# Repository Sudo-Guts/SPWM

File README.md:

# SPWM — Inversor trifásico

Proyecto de control y etapa de potencia de un inversor trifásico con modulación sinusoidal por ancho de pulso (SPWM).

## Objetivo

Generar tres señales de control con desfases de 120 grados mediante un microcontrolador ATmega328P, para gobernar las tres ramas de un inversor trifásico mediante drivers de compuerta.

## Hardware actual

- Microcontrolador: ATmega328P.
- Cristal en el esquema: 16 MHz. Los fusibles y la frecuencia efectiva aún deben verificarse.
- Drivers: tres IR2109.
- Etapa de potencia: seis MOSFET. El esquema identifica IRF540N; el componente físico previsto es IRF640N. Es necesario comprobar compatibilidad de pinout, huella, manejo de compuerta y especificaciones antes de validar la placa.
- Alimentación de potencia prevista: 28 V, fuente externa limitada.

## Estructura

```text
SPWM/
├── .gitignore
├── README.md
├── C0DE/
│   ├── Makefile
│   ├── inc/
│   ├── src/
│   └── out/
├── DOC/
│   └── CheckList.txt
├── PCB/
│   ├── SPWM.kicad_pro
│   ├── SPWM.kicad_sch
│   ├── SPWM.kicad_pcb
│   └── fabrication/
└── SIM/
    ├── psim/
    └── spice/
        └── models/
```

- **C0DE/**: firmware y compilación con AVR-GCC y GNU Make.
- **DOC/**: seguimiento del proyecto mediante `CheckList.txt`, tareas por etapas y criterios de validación.
- **PCB/**: proyecto editable de KiCad; `fabrication/` contiene archivos de salida existentes, no aprobados todavía para fabricar.
- **SIM/psim/**: modelos y circuitos de simulación en PSIM.
- **SIM/spice/**: simulaciones eléctricas SPICE; `models/` guarda los modelos de componentes utilizados.

## Estado del borrador

El firmware incluido es solo un punto de partida que permanece sin PWM ni habilitación de los drivers. No representa la implementación SPWM final. Los archivos de KiCad se recuperaron del proyecto existente en Drive. Falta comprobar ERC/DRC, huellas, pads, asignación de pines, conexión de potencia y sincronización PWM antes de usar la placa o los Gerbers para fabricar.

## Compilación (cuando se disponga de Linux + avr-gcc)

```sh
cd C0DE
make
make size
make clean
```

El Makefile supone F_CPU = 16 MHz para la compilación; verificar primero la fuente de reloj real y los fusibles del ATmega328P.

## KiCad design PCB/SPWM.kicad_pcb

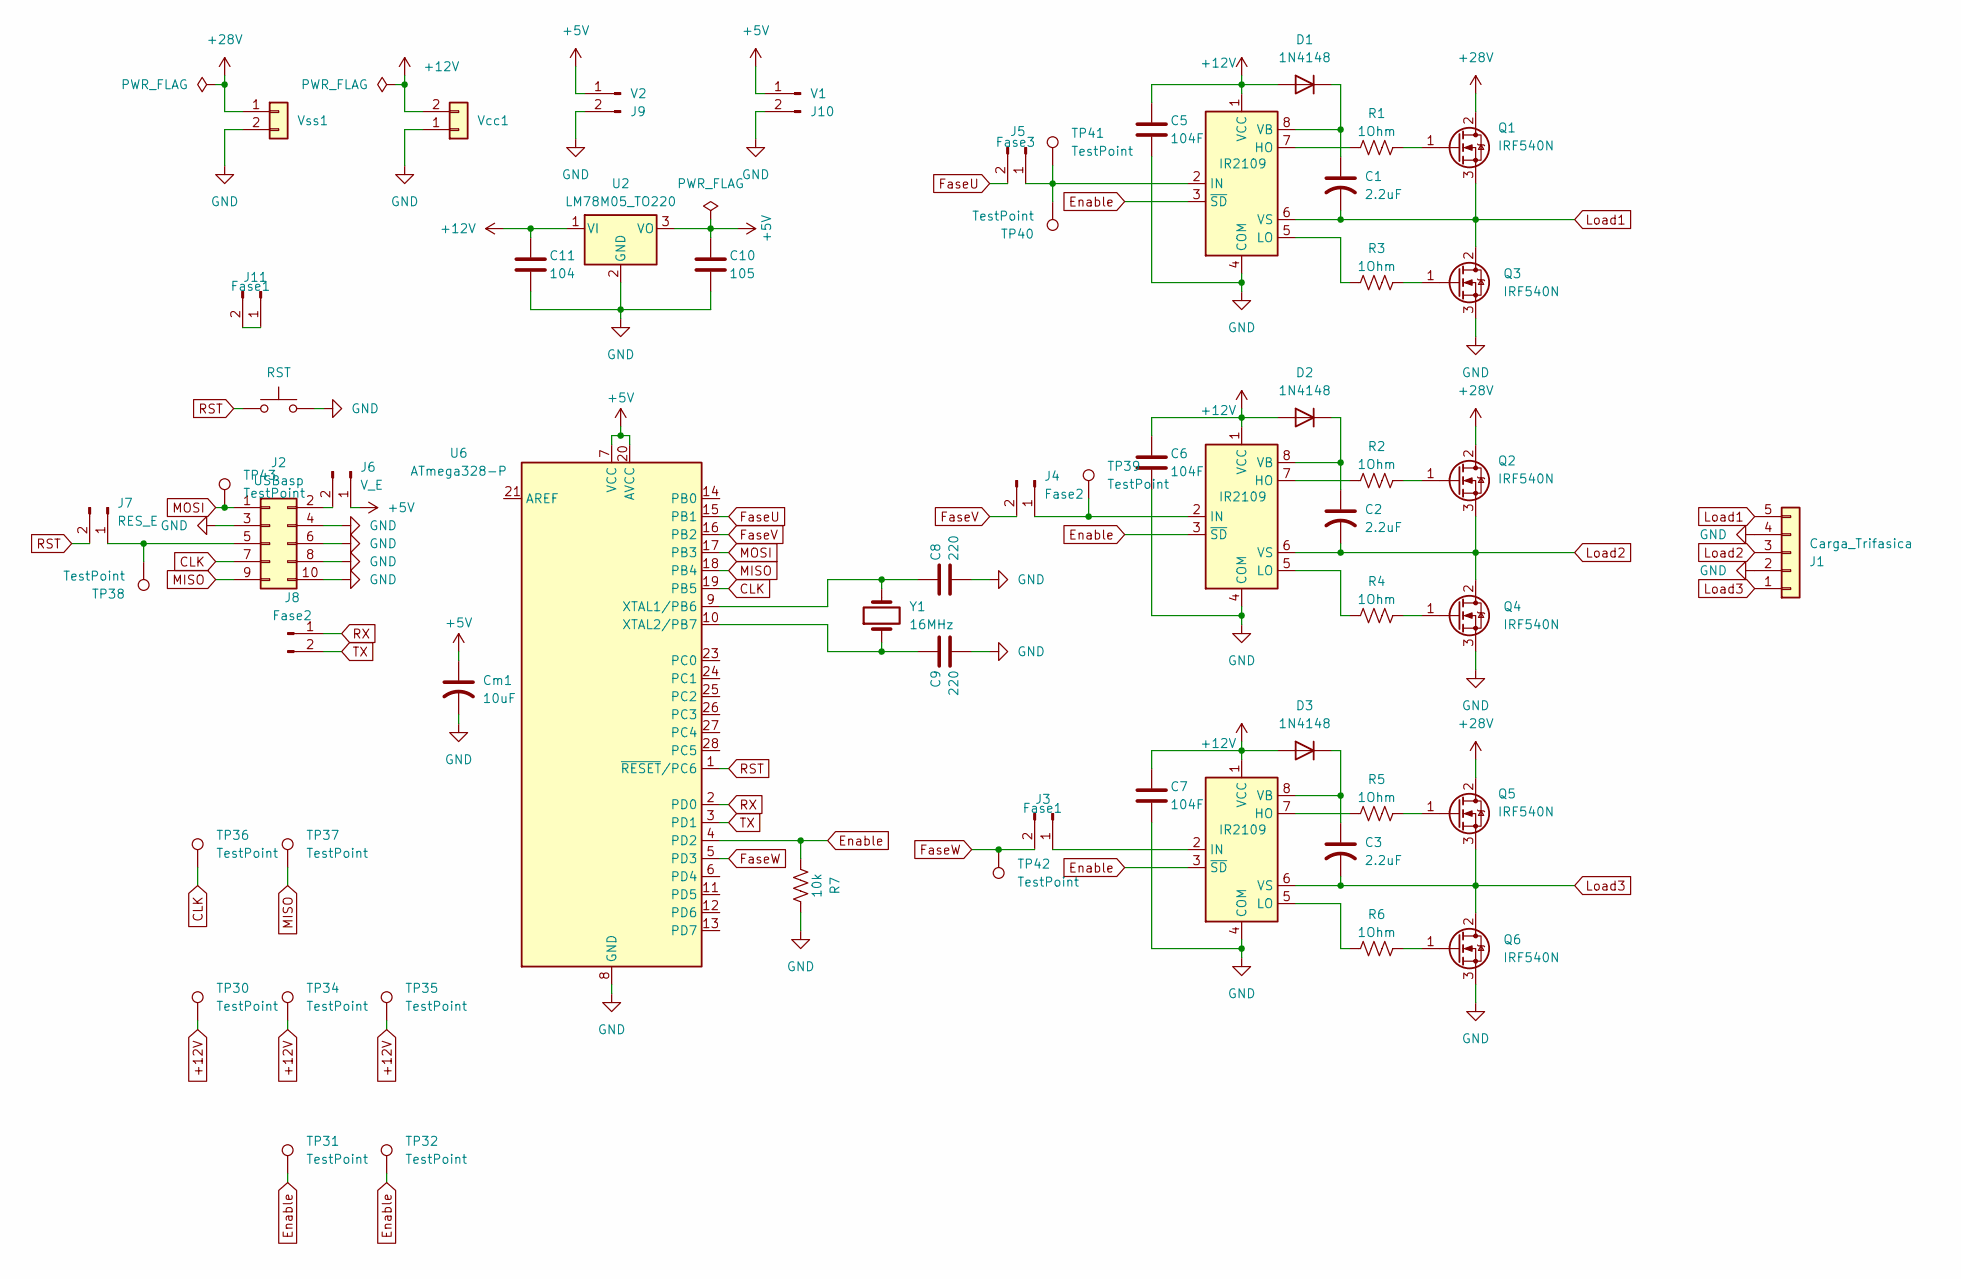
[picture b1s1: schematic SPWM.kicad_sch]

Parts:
C1, C2, C3: 2.2uF; CP_Radial_D4.0mm_P2.00mm
C5, C6, C7: 104F; CP_Radial_Tantal_D5.0mm_P5.00mm
C8, C9: 220; CP_Radial_Tantal_D5.0mm_P5.00mm
C10: 105; CP_Radial_Tantal_D5.0mm_P5.00mm
C11: 104; CP_Radial_Tantal_D5.0mm_P5.00mm
Cm1: 10uF; CP_Radial_D4.0mm_P2.00mm
D1, D2, D3: 1N4148; D_DO-35_SOD27_P7.62mm_Horizontal
J1: Carga_Trifasica; TerminalBlock_MaiXu_MX126-5.0-05P_1x05_P5.00mm
J2: USBasp; IDC-Header_2x05_P2.54mm_Vertical
J3, J11: Fase1; PinHeader_1x02_P2.54mm_Vertical
J4, J8: Fase2; PinHeader_1x02_P2.54mm_Vertical
J5: Fase3; PinHeader_1x02_P2.54mm_Vertical
J6: V_E; PinHeader_1x02_P2.54mm_Vertical
J7: RES_E; PinHeader_1x02_P2.54mm_Vertical
J9: V2; PinHeader_1x02_P2.54mm_Vertical
J10: V1; PinHeader_1x02_P2.54mm_Vertical
Q1, Q2, Q3, Q4, Q5, Q6: IRF540N; TO-220-3_Vertical
R1, R2, R3, R4, R5, R6: 1Ohm; R_Axial_DIN0309_L9.0mm_D3.2mm_P12.70mm_Horizontal
R7: 10k; R_Axial_DIN0309_L9.0mm_D3.2mm_P12.70mm_Horizontal
SW1: RST; SW_PUSH_6mm_H7.3mm
TP30, TP31, TP32, TP34, TP35, TP36, TP37, TP38, TP39, TP40, TP41, TP42, TP43: TestPoint; TestPoint_Bridge_Pitch7.62mm_Drill1.3mm
U1, U4, U5: IR2109; DIP-8_W7.62mm_Socket
U2: LM78M05_TO220; TO-220-3_Vertical
U6: ATmega328-P; DIP-28_W7.62mm
Vcc1: Conn_01x02; TerminalBlock_MaiXu_MX126-5.0-02P_1x02_P5.00mm
Vss1: Conn_01x02; TerminalBlock_MaiXu_MX126-5.0-02P_1x02_P5.00mm
Y1: 16MHz; Crystal_HC49-4H_Vertical

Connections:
+5V: C10.1, Cm1.1, J6.1, J9.1 (Pin_1_1), J10.1 (Pin_1_1), U2.3 (VO), U6.7 (VCC), U6.20 (AVCC)
+12V: C5.1, C6.1, C7.1, C11.1, D1.2 (A), D2.2 (A), D3.2 (A), TP30.1 (1_1), TP34.1 (1_1), TP35.1 (1_1), U1.1 (VCC), U2.1 (VI), U4.1 (VCC), U5.1 (VCC), Vcc1.2 (Pin_2_2)
+28V: Q1.2 (D), Q2.2 (D), Q5.2 (D), Vss1.1 (Pin_1_1)
CLK: J2.7, TP36.1 (1_1), U6.19 (PB5)
Enable: R7.1, TP31.1 (1_1), TP32.1 (1_1), U1.3 (~SD), U4.3 (~SD), U5.3 (~SD), U6.4 (PD2)
FaseU: J5.2, U6.15 (PB1)
FaseV: J4.2, U6.16 (PB2)
FaseW: J3.2, TP42.1 (1_1), U6.5 (PD3)
Load1: C1.2, J1.5, Q1.3 (S), Q3.2 (D), U1.6 (VS)
Load2: C2.2, J1.3, Q2.3 (S), Q4.2 (D), U4.6 (VS)
Load3: C3.2, J1.1, Q5.3 (S), Q6.2 (D), U5.6 (VS)
MISO: J2.9, TP37.1 (1_1), U6.18 (PB4)
MOSI: J2.1, TP43.1 (1_1), U6.17 (PB3)
unnamed: C1.1, D1.1 (K), U1.8 (VB)
unnamed: C2.1, D2.1 (K), U4.8 (VB)
unnamed: C3.1, D3.1 (K), U5.8 (VB)
unnamed: J2.2, J6.2
unnamed: J2.5, J7.1, TP38.1 (1_1)
unnamed: J3.1, U5.2 (IN)
unnamed: J4.1, TP39.1 (1_1), U4.2 (IN)
unnamed: J5.1, TP40.1 (1_1), TP41.1 (1_1), U1.2 (IN)
unnamed: J11.1, J11.2
unnamed: Q1.1 (G), R1.2
unnamed: Q2.1 (G), R2.2
unnamed: Q3.1 (G), R3.2
unnamed: Q4.1 (G), R4.2
unnamed: Q5.1 (G), R5.2
unnamed: Q6.1 (G), R6.2
unnamed: R1.1, U1.7 (HO)
unnamed: R3.1, U1.5 (LO)
unnamed: R2.1, U4.7 (HO)
unnamed: R4.1, U4.5 (LO)
unnamed: R5.1, U5.7 (HO)
unnamed: R6.1, U5.5 (LO)
unnamed: C8.1, U6.9 (XTAL1/PB6), Y1.2
unnamed: C9.1, U6.10 (XTAL2/PB7), Y1.1
RST: J7.2, SW1.1 (1_1), U6.1 (~RESET/PC6)
RX: J8.1, U6.2 (PD0)
TX: J8.2, U6.3 (PD1)

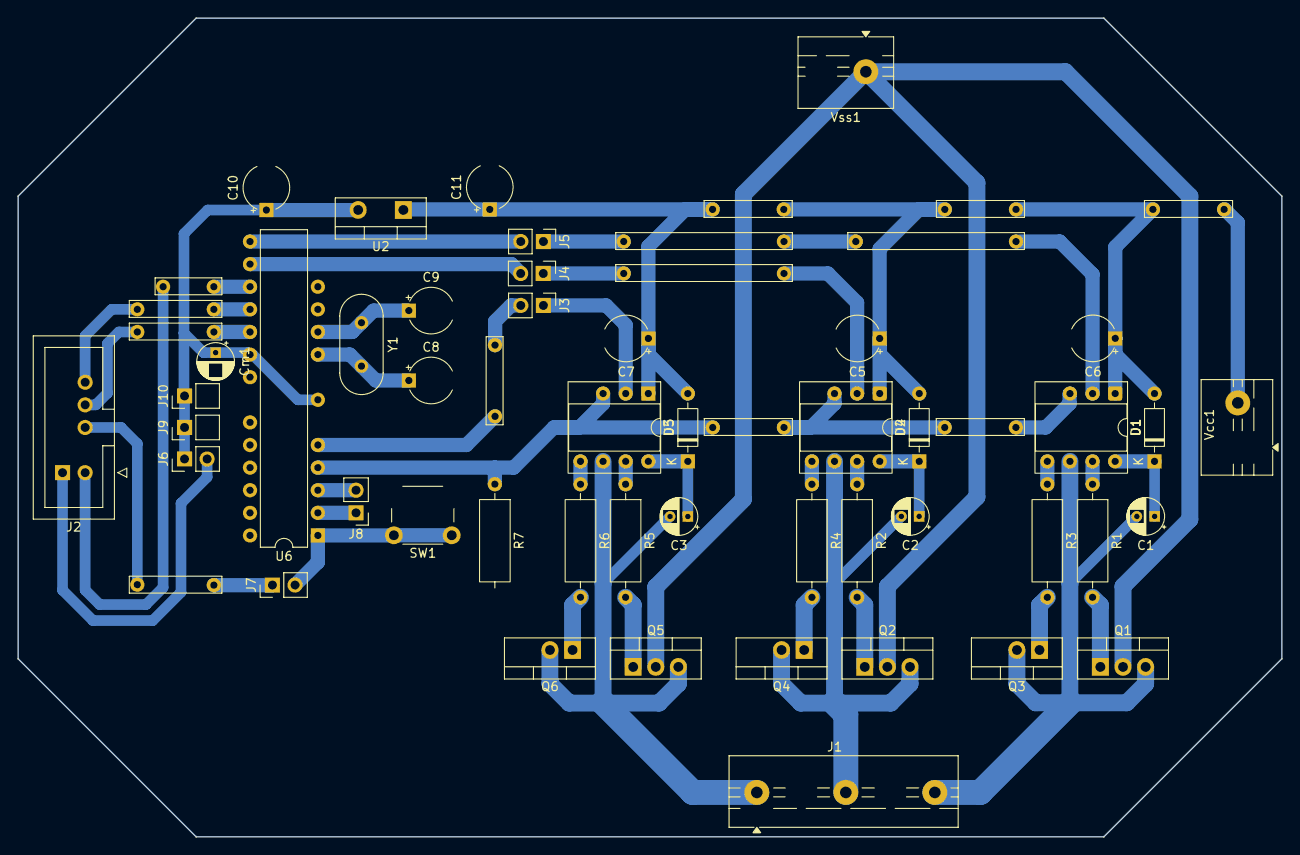
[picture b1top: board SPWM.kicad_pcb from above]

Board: 2 copper layers, 142.0 x 92.0 mm, 59 parts (0 on the bottom side), 38 nets.
